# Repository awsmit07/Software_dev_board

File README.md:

View this project on [CADLAB.io](https://cadlab.io/project/27065). 

# Software_dev_board

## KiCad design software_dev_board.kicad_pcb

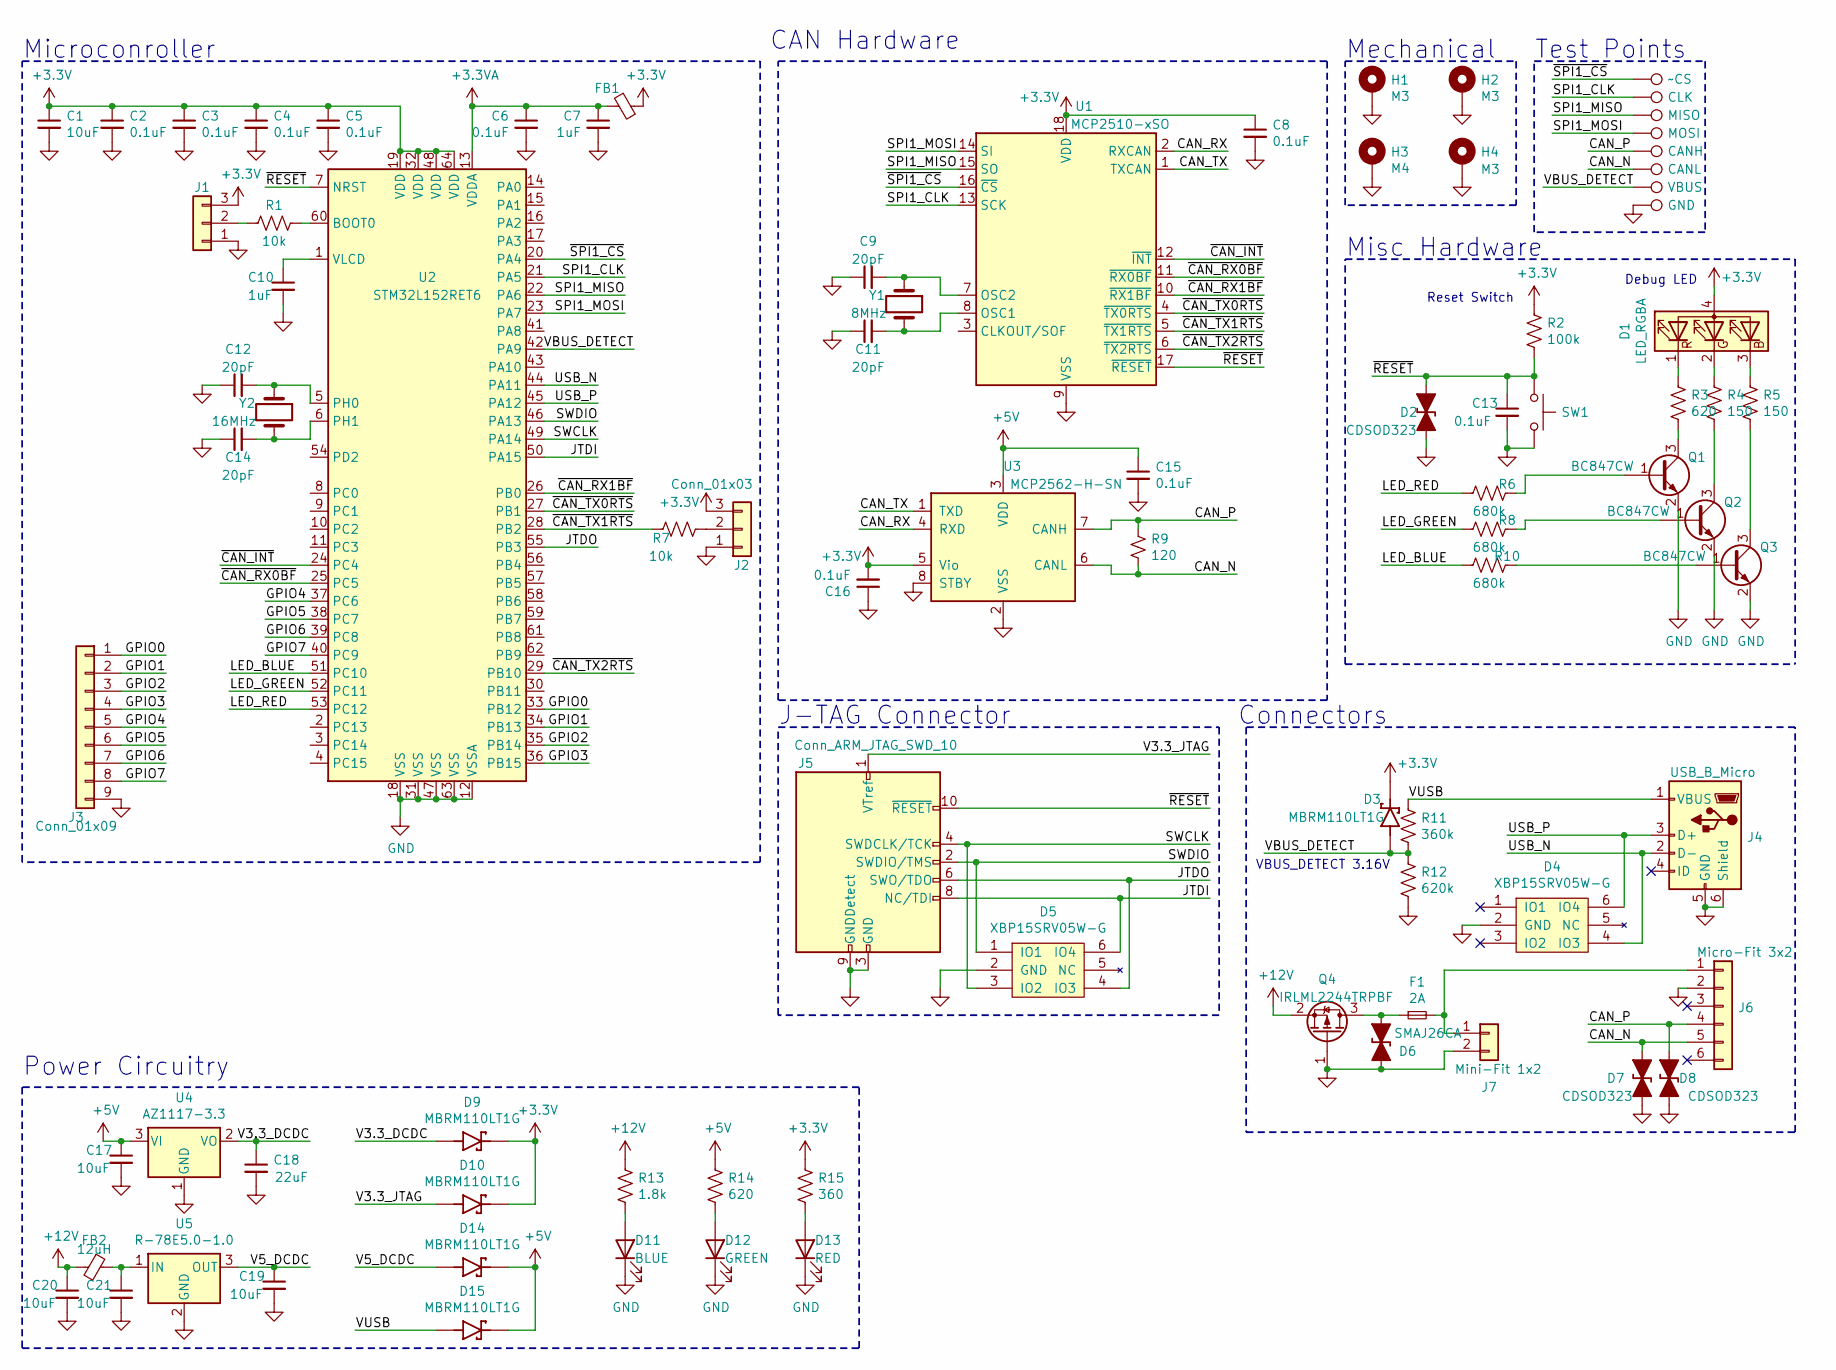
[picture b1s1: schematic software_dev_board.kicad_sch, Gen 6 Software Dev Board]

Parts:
C1, C17, C19, C20, C21: 10uF; C_0603_1608Metric
C2, C3, C4, C5, C6, C8, C13, C15, C16: 0.1uF; C_0603_1608Metric
C7, C10: 1uF; C_0603_1608Metric
C9, C11, C12, C14: 20pF; C_0603_1608Metric
C18: 22uF; C_0603_1608Metric; Digikey 1276-2867-2-ND
D1: LED_RGBA; LED_0606_1616Metric; Digikey 1080-1551-2-ND
D2, D7, D8: CDSOD323; D_SOD-323_HandSoldering
D3, D9, D10, D14, D15: MBRM110LT1G; DIO_MBRM110LT1G; PARTREV 2; Digikey MBRM110LT1GOSTR-ND
D4, D5: XBP15SRV05W-G; SOT-23-6_Handsoldering; Digikey 893-1422-2-ND
D6: SMAJ26CA; D_SMA_Handsoldering; Digikey SMAJ26CALFTR-ND
D11: BLUE; LED_0603_1608Metric_Pad1.05x0.95mm_HandSolder; Digikey 732-4966-2-ND
D12: GREEN; LED_0603_1608Metric_Pad1.05x0.95mm_HandSolder; Digikey 732-4980-2-ND
D13: RED; LED_0603_1608Metric_Pad1.05x0.95mm_HandSolder; Digikey 732-4979-2-ND
F1: 2A; Fuseholder_Littlefuse_0154; Digikey F6778TR-ND
FB1: 600Ohm @ 100MHz, 200mOhm DC; L_0603_1608Metric
FB2: 12uH; L_0603_1608Metric
H1, H2, H4: M3; MountingHole_3.2mm_M3_Pad_Via
H3: M4; MountingHole_3.2mm_M3_Pad_Via
J1, J2: Conn_01x03; PinHeader_1x03_P2.54mm_Vertical
J3: Conn_01x09; PinHeader_1x09_P2.54mm_Vertical
J4: USB_B_Micro; USB_Micro-B_Amphenol_10118194_Horizontal; Digikey 609-4618-1-ND
J5: Conn_ARM_JTAG_SWD_10; PinHeader_ARM_10pin_debug; Digikey 1175-1629-ND
J6: Micro-Fit 3x2; Molex_Micro-Fit_3.0_43045-0600_2x03_P3.00mm_Horizontal
J7: Mini-Fit 1x2; Molex_Mini-Fit_Jr_5569-02A2_2x01_P4.20mm_Horizontal
Q1, Q2, Q3: BC847CW; SOT-323_SC-70; Digikey 1727-4312-1-ND
Q4: IRLML2244TRPBF; SOT-23; Digikey DMP3125L-7DITR-ND
R1, R7: 10k; R_0603_1608Metric
R2: 100k; R_0603_1608Metric
R3, R14: 620; R_0603_1608Metric
R4, R5: 150; R_0603_1608Metric
R6, R8, R10: 680k; R_0603_1608Metric
R9: 120; R_0603_1608Metric
R11: 360k; R_0603_1608Metric
R12: 620k; R_0603_1608Metric
R13: 1.8k; R_0603_1608Metric
R15: 360; R_0603_1608Metric
SW1: SW_Push; SW_Push_1P1T_NO_6x6mm_H9.5mm; Digikey CKN9085TR-ND
TP1: ~CS; TestPoint_1mm
TP2: CLK; TestPoint_1mm
TP3: MISO; TestPoint_1mm
TP4: MOSI; TestPoint_1mm
TP5: CANH; TestPoint_1mm
TP6: CANL; TestPoint_1mm
TP7: VBUS; TestPoint_1mm
TP8: GND; TestPoint_1mm
U1: MCP2510-xSO; SOIC-18W_7.5x11.6mm_P1.27mm; Digikey MCP2510-I/SO-ND
U2: STM32L152RET6; LQFP-64_10x10mm_P0.5mm; Digikey 497-15830-ND
U3: MCP2562-H-SN; SOIC-8_3.9x4.9mm_P1.27mm
U4: AZ1117-3.3; SOT-223-3_TabPin2; Digikey AZ1117IH-3.3TRG1DITR-ND
U5: R-78E5.0-1.0; Converter_DCDC_RECOM_R-78E-0.5_THT; Digikey 945-2201-ND
Y1: 8MHz; Crystal_HC49-U_Vertical
Y2: 16MHz; Crystal_HC49-U_Vertical

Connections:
+3.3VA: C6.1, C7.1, FB1.1, U2.13 (VDDA)
+3V3: C1.1, C2.1, C3.1, C4.1, C5.1, C8.1, C16.2, D1.4 (A), D3.1, D9.1, D10.1, FB1.2, J1.3, J2.3, R2.1, R15.1, U1.18 (VDD), U2.19 (VDD), U2.32 (VDD), U2.48 (VDD), U2.64 (VDD), U3.5 (Vio)
+5V: C15.1, C17.1, D14.1, D15.1, R14.1, U3.3 (VDD), U4.3 (VI)
+12V: C20.1, FB2.2, Q4.2 (S), R13.1
/CAN_N: D7.1 (A1), J6.5, R9.2, TP6.1, U3.6 (CANL)
/CAN_P: D8.1 (A1), J6.4, R9.1, TP5.1, U3.7 (CANH)
/CAN_RX: U1.2 (RXCAN), U3.4 (RXD)
/CAN_TX: U1.1 (TXCAN), U3.1 (TXD)
/GPIO0: J3.1, U2.33 (PB12)
/GPIO1: J3.2, U2.34 (PB13)
/GPIO2: J3.3, U2.35 (PB14)
/GPIO3: J3.4, U2.36 (PB15)
/GPIO4: J3.5, U2.37 (PC6)
/GPIO5: J3.6, U2.38 (PC7)
/GPIO6: J3.7, U2.39 (PC8)
/GPIO7: J3.8, U2.40 (PC9)
/JTDI: D5.6 (IO4), J5.8 (NC/TDI), U2.50 (PA15)
/JTDO: D5.4 (IO3), J5.6 (SWO/TDO), U2.55 (PB3)
/LED_BLUE: R10.2, U2.51 (PC10)
/LED_GREEN: R8.2, U2.52 (PC11)
/LED_RED: R6.2, U2.53 (PC12)
/SPI1_CLK: TP2.1, U1.13 (SCK), U2.21 (PA5)
/SPI1_MISO: TP3.1, U1.15 (SO), U2.22 (PA6)
/SPI1_MOSI: TP4.1, U1.14 (SI), U2.23 (PA7)
/SWCLK: D5.3 (IO2), J5.4 (SWDCLK/TCK), U2.49 (PA14)
/SWDIO: D5.1 (IO1), J5.2 (SWDIO/TMS), U2.46 (PA13)
/USB_N: D4.4 (IO3), J4.2 (D-), U2.44 (PA11)
/USB_P: D4.6 (IO4), J4.3 (D+), U2.45 (PA12)
/V3.3_DCDC: C18.1, D9.2, U4.2 (VO)
/V3.3_JTAG: D10.2, J5.1 (VTref)
/V5_DCDC: C19.1, D14.2, U5.3 (OUT)
/VBUS_DETECT: D3.2, R11.2, R12.1, TP7.1, U2.42 (PA9)
/VUSB: D15.2, J4.1 (VBUS), R11.1
/~CAN_INT: U1.12 (~INT), U2.24 (PC4)
/~CAN_RX0BF: U1.11 (~RX0BF), U2.25 (PC5)
/~CAN_RX1BF: U1.10 (~RX1BF), U2.26 (PB0)
/~CAN_TX0RTS: U1.4 (~TX0RTS), U2.27 (PB1)
/~CAN_TX1RTS: R7.2, U1.5 (~TX1RTS), U2.28 (PB2)
/~CAN_TX2RTS: U1.6 (~TX2RTS), U2.29 (PB10)
/~RESET: C13.1, D2.1 (A1), J5.10 (~RESET), R2.2, SW1.1, U1.17 (~RESET), U2.7 (NRST)
/~SPI1_CS: TP1.1, U1.16 (~CS), U2.20 (PA4)
GND: C1.2, C2.2, C3.2, C4.2, C5.2, C6.2, C7.2, C8.2, C9.1, C10.2, C11.1, C12.1, C13.2, C14.1, C15.2, C16.1, C17.2, C18.2, C19.2, C20.2, C21.2, D2.2 (A2), D4.2 (GND), D5.2 (GND), D6.2 (A2), D7.2 (A2), D8.2 (A2), D11.1 (K), D12.1 (K), D13.1 (K), H1.1, H2.1, H3.1, H4.1, J1.1, J2.1, J3.9, J4.5 (GND), J4.6 (Shield), J5.3 (GND), J5.5 (GND), J5.9 (GNDDetect), J6.2, J7.2, Q1.2 (E), Q2.2 (E), Q3.2 (E), Q4.1 (G), R12.2, SW1.2, TP8.1, U1.9 (VSS), U2.12 (VSSA), U2.18 (VSS), U2.31 (VSS), U2.47 (VSS), U2.63 (VSS), U3.2 (VSS), U3.8 (STBY), U4.1 (GND), U5.2 (GND)
unnamed: C9.2, U1.7 (OSC2), Y1.1
unnamed: C10.1, U2.1 (VLCD)
unnamed: C11.2, U1.8 (OSC1), Y1.2
unnamed: C12.2, U2.5 (PH0), Y2.1
unnamed: C14.2, U2.6 (PH1), Y2.2
unnamed: C21.1, FB2.1, U5.1 (IN)
unnamed: D1.1 (RK), R3.1
unnamed: D1.2 (GK), R4.1
unnamed: D1.3 (BK), R5.1
unnamed: D11.2 (A), R13.2
unnamed: D12.2 (A), R14.2
unnamed: D13.2 (A), R15.2
unnamed: D6.1 (A1), F1.1, Q4.3 (D)
unnamed: F1.2, J6.1, J7.1
unnamed: J1.2, R1.1
unnamed: J2.2, R7.1
unnamed: Q1.1 (B), R6.1
unnamed: Q1.3 (C), R3.2
unnamed: Q2.1 (B), R8.1
unnamed: Q2.3 (C), R4.2
unnamed: Q3.1 (B), R10.1
unnamed: Q3.3 (C), R5.2
unnamed: R1.2, U2.60 (BOOT0)

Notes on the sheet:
VBUS_DETECT 3.16V
Microconroller
J-TAG Connector
CAN Hardware
Mechanical
Reset Switch
Power Circuitry
Misc Hardware
Connectors
Debug LED
Test Points

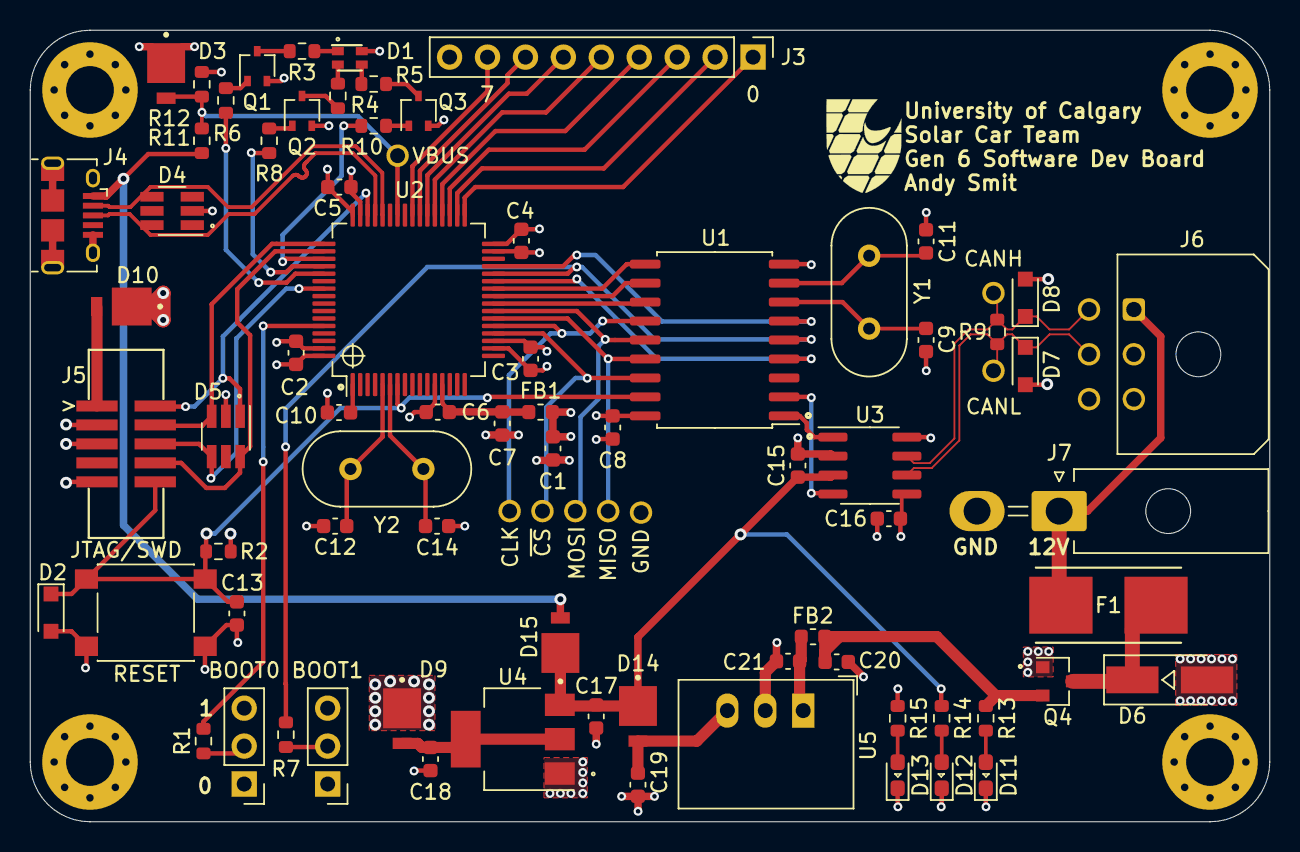
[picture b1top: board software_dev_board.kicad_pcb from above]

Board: 4 copper layers, 83.0 x 53.0 mm, 85 parts (0 on the bottom side), 65 nets.

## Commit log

2023-06-19 Backlink to CADLAB.io has been added.
